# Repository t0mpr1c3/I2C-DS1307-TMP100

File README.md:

I2C-DS1307-TMP100
=================

Daisy chainable breakout board for DS1307 real time clock and/or TMP100 thermometer. For dual use, or simultaneous use allowing temperature dependent calibration of the RTC.

Released under the [Creative Commons License Attribution-ShareAlike 3.0](http://creativecommons.org/licenses/by-sa/3.0/)

Version history
---------------

_IT01_

First version.

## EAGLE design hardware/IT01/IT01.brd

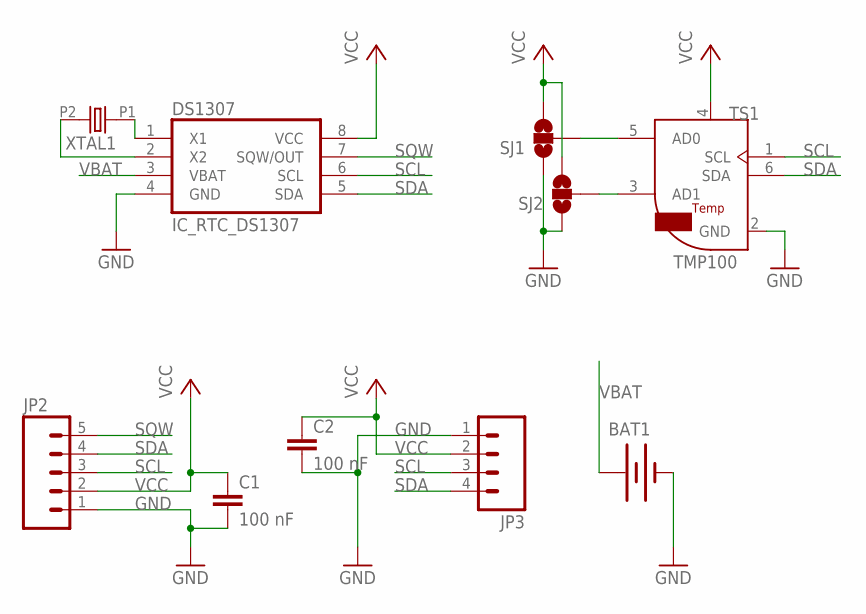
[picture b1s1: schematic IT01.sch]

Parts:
BAT1: BATTERY12MM; BATTCON_12MM
C1, C2: 100 nF; C0805
DS1307: IC_RTC_DS1307; SO-8
JP2: M05PTH; 1X05
JP3: M04PTH; 1X04
SJ1, SJ2: SOLDERJUMPER_2WAY-OLDT; SJ_2
TS1: TMP100; SOT23-6
XTAL1: OSC-XTAL-TC-38; TC-38

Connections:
AD0: SJ1.2, TS1.5 (AD0)
AD1: SJ2.2, TS1.3 (AD1)
GND: BAT1.GND (-), C1.2, C2.2, DS1307.4 (GND), JP2.1, JP3.1, SJ1.1, SJ2.1, TS1.2 (GND)
unnamed: DS1307.1 (X1), XTAL1.P1 (1)
unnamed: DS1307.2 (X2), XTAL1.P2 (2)
SCL: DS1307.6 (SCL), JP2.3, JP3.3, TS1.1 (SCL)
SDA: DS1307.5 (SDA), JP2.4, JP3.4, TS1.6 (SDA)
SQW: DS1307.7 (SQW/OUT), JP2.5
VBAT: BAT1.PWR@1 (+), DS1307.3 (VBAT)
VCC: C1.1, C2.1, DS1307.8 (VCC), JP2.2, JP3.2, SJ1.3, SJ2.3, TS1.4 (UCC)

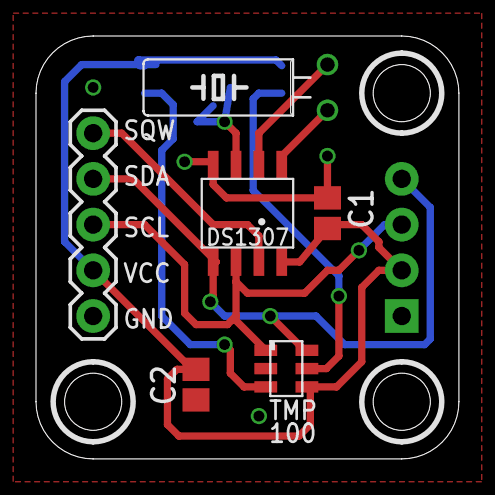
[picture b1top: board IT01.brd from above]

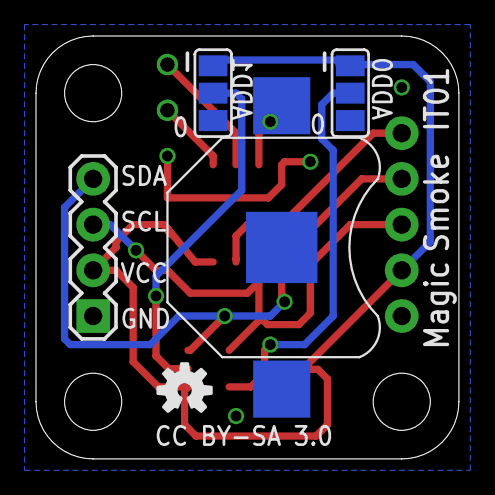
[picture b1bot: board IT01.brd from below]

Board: 4 copper layers, 23.5 x 23.5 mm, 11 parts (5 on the bottom side), 10 nets.

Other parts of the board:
U$1: OSHW-LOGO-S

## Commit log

2013-11-18 reversed header on TMP100 side
2013-11-20 stop over crystal pads
2013-12-01 tweak gerbers
2013-12-03 IT01 for Seeedstudio
2013-12-24 IT01 Elecrow order

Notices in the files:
hardware/IT01/IT01.brd:
CC BY-SA 3.0
parts and their libraries:
SparkFun: Licensing: CC v3.0 Share-Alike You are welcome to use this library for commercial purposes.
